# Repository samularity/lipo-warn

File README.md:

lipo-alert
=========

this project is as small lipo alert system with cell detection
its based on a Attiny13A and its used in my RC-Plane
You are free to choos the alert-actor, you can use LEDs or Acustic system

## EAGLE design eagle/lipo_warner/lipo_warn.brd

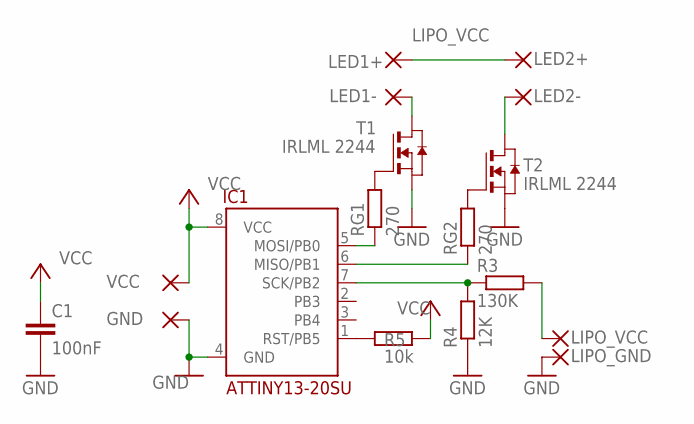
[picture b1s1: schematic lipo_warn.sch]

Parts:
C1: 100nF; C1206
GND: SMD2; SMD1,27-2,54
IC1: ATTINY13-20SU; SOIC8
LED1+, LED1-, LED2+, LED2-: WIREPADSMD1,27-254; SMD1,27-2,54
LIPO_GND: WIREPADSMD5-2,5; 5-2,5
LIPO_VCC: WIREPADSMD5-2,5; 5-2,5
R3: 130K; M1206
R4: 12K; M1206
R5: 10k; M1206
RG1, RG2: 270; M1206
T1, T2: IRLML 2244; SOT-23
VCC: SMD2; SMD1,27-2,54

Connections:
GND: C1.2, GND.1, IC1.4 (GND), LIPO_GND.1, R4.1, T1.2 (S), T2.2 (S)
LIPO_VCC: LED1+.1, LED2+.1
unnamed: IC1.1 (RST/PB5), R5.1
unnamed: IC1.5 (MOSI/PB0), RG1.1
unnamed: IC1.6 (MISO/PB1), RG2.1
unnamed: IC1.7 (SCK/PB2), R3.1, R4.2
unnamed: LIPO_VCC.1, R3.2
unnamed: LED1-.1, T1.1 (D)
unnamed: RG1.2, T1.3 (G)
unnamed: RG2.2, T2.3 (G)
unnamed: LED2-.1, T2.1 (D)
VCC: C1.1, IC1.8 (VCC), R5.2, VCC.1

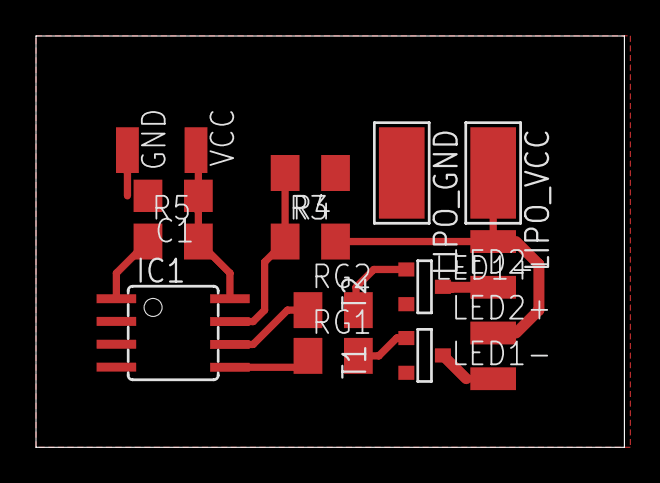
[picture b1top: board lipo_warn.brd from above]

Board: 2 copper layers, 32.7 x 22.9 mm, 17 parts (0 on the bottom side), 12 nets.

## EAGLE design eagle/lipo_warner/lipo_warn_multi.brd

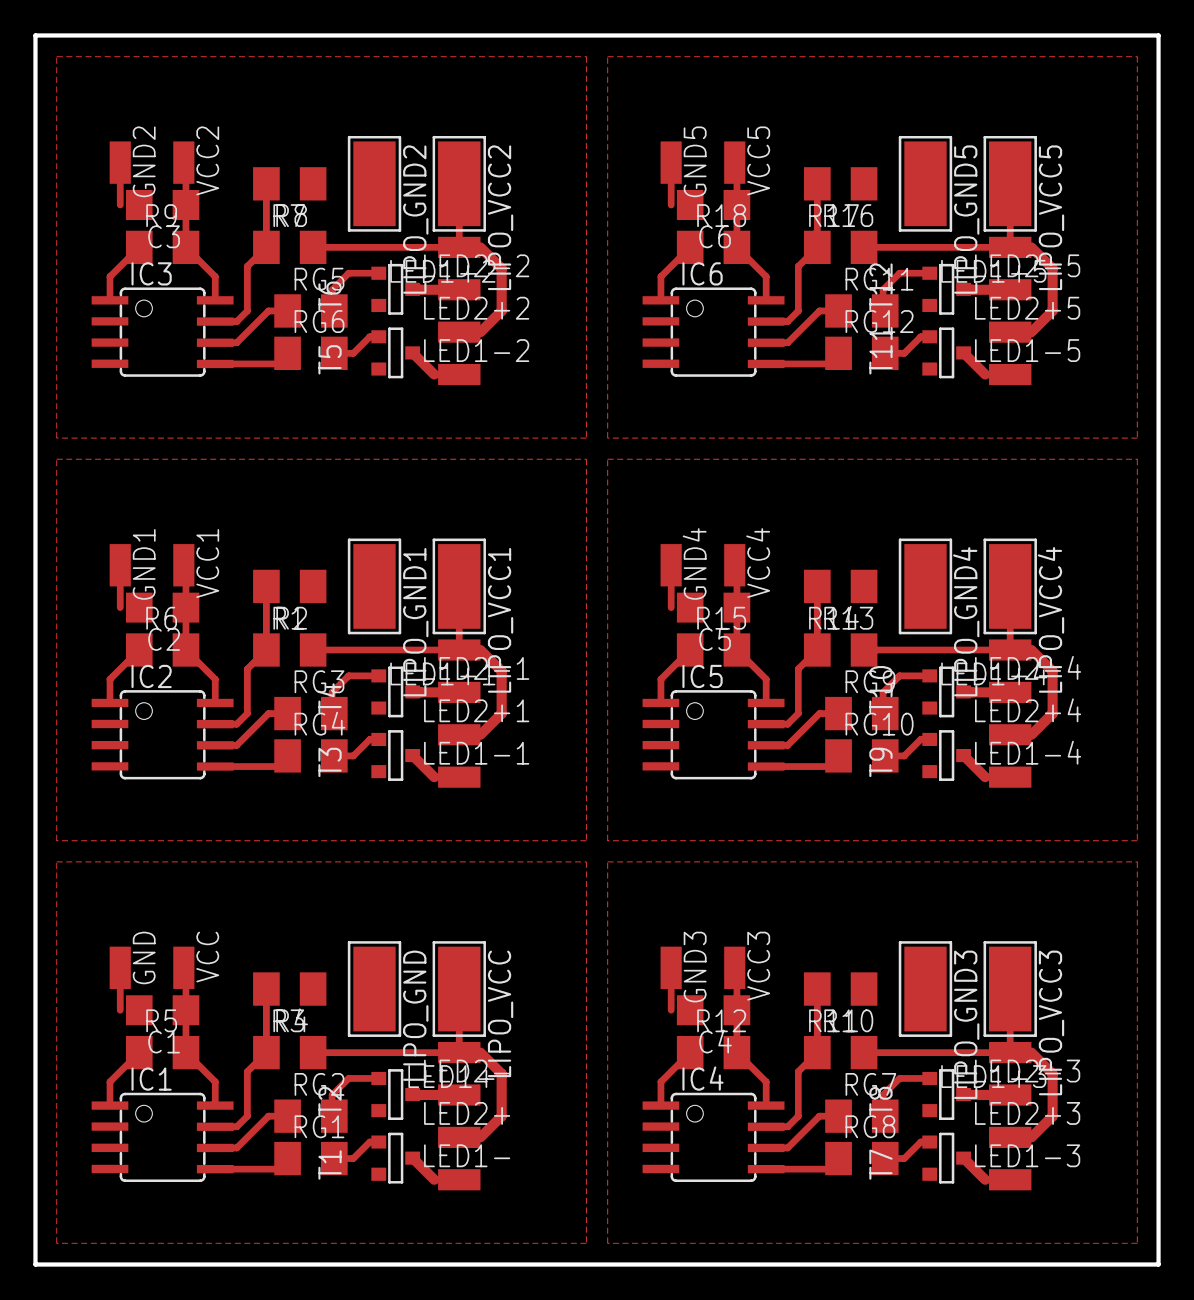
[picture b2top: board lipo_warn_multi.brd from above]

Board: 2 copper layers, 67.3 x 73.7 mm, 102 parts (0 on the bottom side), 72 nets.

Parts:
C1, C2, C3, C4, C5, C6: 100nF; C1206
GND, GND1, GND2, GND3, GND4, GND5: SMD1,27-2,54
IC1, IC2, IC3, IC4, IC5, IC6: ATTINY13-20SU; SOIC8
LED1+, LED1+1, LED1+2, LED1+3, LED1+4, LED1+5, LED1-, LED1-1, LED1-2, LED1-3, LED1-4, LED1-5, LED2+, LED2+1, LED2+2, LED2+3, LED2+4, LED2+5, LED2-, LED2-1, LED2-2, LED2-3, LED2-4, LED2-5: WIREPADSMD1,27-254; SMD1,27-2,54
LIPO_GND, LIPO_GND1, LIPO_GND2, LIPO_GND3, LIPO_GND4, LIPO_GND5: WIREPADSMD5-2,5; 5-2,5
LIPO_VCC, LIPO_VCC1, LIPO_VCC2, LIPO_VCC3, LIPO_VCC4, LIPO_VCC5: WIREPADSMD5-2,5; 5-2,5
R1, R3, R7, R10, R13, R16: 130K; M1206
R2, R4, R8, R11, R14, R17: 12K; M1206
R5, R6, R9, R12, R15, R18: 10k; M1206
RG1, RG2, RG3, RG4, RG5, RG6, RG7, RG8, RG9, RG10, RG11, RG12: 270; M1206
T1, T2, T3, T4, T5, T6, T7, T8, T9, T10, T11, T12: IRLML 2244; SOT-23
VCC, VCC1, VCC2, VCC3, VCC4, VCC5: SMD1,27-2,54

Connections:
GND: C1.2, GND.1, IC1.4, LIPO_GND.1, R4.1, T1.2, T2.2
GND1: C2.2, GND1.1, IC2.4, LIPO_GND1.1, R2.1, T3.2, T4.2
GND2: C3.2, GND2.1, IC3.4, LIPO_GND2.1, R8.1, T5.2, T6.2
GND3: C4.2, GND3.1, IC4.4, LIPO_GND3.1, R11.1, T7.2, T8.2
GND4: C5.2, GND4.1, IC5.4, LIPO_GND4.1, R14.1, T9.2, T10.2
GND5: C6.2, GND5.1, IC6.4, LIPO_GND5.1, R17.1, T11.2, T12.2
LIPO_VCC: LED1+.1, LED2+.1
LIPO_VCC1: LED1+1.1, LED2+1.1
LIPO_VCC2: LED1+2.1, LED2+2.1
LIPO_VCC3: LED1+3.1, LED2+3.1
LIPO_VCC4: LED1+4.1, LED2+4.1
LIPO_VCC5: LED1+5.1, LED2+5.1
unnamed: IC1.1, R5.1
unnamed: IC1.5, RG1.1
unnamed: IC1.6, RG2.1
unnamed: IC1.7, R3.1, R4.2
unnamed: LIPO_VCC.1, R3.2
unnamed: IC2.1, R6.1
unnamed: LED1-.1, T1.1
unnamed: RG1.2, T1.3
unnamed: RG2.2, T2.3
unnamed: LED2-.1, T2.1
unnamed: IC2.5, RG4.1
unnamed: IC2.6, RG3.1
unnamed: IC2.7, R1.1, R2.2
unnamed: RG4.2, T3.3
unnamed: RG3.2, T4.3
unnamed: LED1-1.1, T3.1
unnamed: LED2-1.1, T4.1
unnamed: LIPO_VCC1.1, R1.2
unnamed: IC3.1, R9.1
unnamed: IC3.5, RG6.1
unnamed: IC3.6, RG5.1
unnamed: IC3.7, R7.1, R8.2
unnamed: RG6.2, T5.3
unnamed: RG5.2, T6.3
unnamed: LED1-2.1, T5.1
unnamed: LED2-2.1, T6.1
unnamed: LIPO_VCC2.1, R7.2
unnamed: IC4.1, R12.1
unnamed: IC4.5, RG8.1
unnamed: IC4.6, RG7.1
unnamed: IC4.7, R10.1, R11.2
unnamed: RG8.2, T7.3
unnamed: RG7.2, T8.3
unnamed: LED1-3.1, T7.1
unnamed: LED2-3.1, T8.1
unnamed: LIPO_VCC3.1, R10.2
unnamed: IC5.1, R15.1
unnamed: IC5.5, RG10.1
unnamed: IC5.6, RG9.1
unnamed: IC5.7, R13.1, R14.2
unnamed: RG10.2, T9.3
unnamed: RG9.2, T10.3
unnamed: LED1-4.1, T9.1
unnamed: LED2-4.1, T10.1
unnamed: LIPO_VCC4.1, R13.2
unnamed: IC6.1, R18.1
unnamed: IC6.5, RG12.1
unnamed: IC6.6, RG11.1
unnamed: IC6.7, R16.1, R17.2
unnamed: RG12.2, T11.3
unnamed: RG11.2, T12.3
unnamed: LED1-5.1, T11.1
unnamed: LED2-5.1, T12.1
unnamed: LIPO_VCC5.1, R16.2
VCC: C1.1, IC1.8, R5.2, VCC.1
VCC1: C2.1, IC2.8, R6.2, VCC1.1
VCC2: C3.1, IC3.8, R9.2, VCC2.1
VCC3: C4.1, IC4.8, R12.2, VCC3.1
VCC4: C5.1, IC5.8, R15.2, VCC4.1
VCC5: C6.1, IC6.8, R18.2, VCC5.1

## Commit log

2014-10-29 :tada: Added .gitattributes & .gitignore files
2014-10-29 inital commit
    first release
2014-10-29 delete binary stuff
    deleted unused binarys
2014-10-29 inital commit
    release
2014-10-30 add lable
    add label for V0.1
2014-10-30 add multiple boards
    add 6 boards to one layout
2014-11-04 add adc in description
    add comment for better code understanding
2014-11-04 ignore *.b#* eagle error files
    no change in circuit or board
